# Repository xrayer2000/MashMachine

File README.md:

# MashMachine

An automated homebrewing system developed around a modified Vevor mash tun, an ESP32-based controller and custom temperature regulation.

## Introduction

This project has been a great journey for me to learn even more about the subjects covered in the MPSYS (Systems, Control and Mechatronics) programme at Chalmers University of Technology.

I have specifically applied knowledge from two courses:

- **SSY230 – System Identification**
- **SSY285 – Design of Linear Control Systems**

The mash tun has served as a physical test platform for applying system identification and control theory to a real-world thermal system.

## Mash Tun Construction

The starting point for this project was a relatively basic mash tun from Vevor, which only supported simple heating through its original controller.

I decided to modify the vessel and develop a custom control system to improve temperature regulation and automate the brewing process.

The mechanical work involved modifying the stainless-steel vessel, welding components, installing the necessary hardware and constructing an insulated enclosure.

### Fabrication

The following photographs document parts of the fabrication process, including the initial measurements, stainless-steel vessel and welding.

### Welding and Assembly

### Finished Mash Tun

The finished vessel has an insulated exterior to reduce heat losses and improve thermal efficiency.

### Construction Videos

#### Welding

https://github.com/user-attachments/assets/f25a4e15-6e44-4505-bbf4-2bfe34d7de5a

https://github.com/user-attachments/assets/1c13a10b-537a-4cbe-8e05-aff711293a5b

## System Implementation

The original controller was removed and replaced with a custom-built ESP32-based control system.

Several hardware modifications were made:

- A circulation system was added using a pump.
- Piping was installed to allow continuous wort circulation.
- The original control electronics were replaced with an ESP32-based system.

The circulation system improves temperature uniformity and makes the system more suitable for model-based control.

The original system exhibited temperature overshoot of around 2°C. With the new controller, temperature regulation is significantly improved, with essentially no observable overshoot under normal operating conditions.

Additional functionality includes:

- Hop timers
- Mash programs
- Automated process control
- Home Assistant integration

## System Identification

In the System Identification course, I used the mash tun to collect both estimation and validation data.

Using the System Identification Toolbox in MATLAB, I derived state-space models for three different operating points:

- 50°C
- 65°C
- 70°C

### Estimation Data

### Validation Data

### ARMAX Model

All system matrices were computed in MATLAB and then implemented directly on the ESP32. The computational work was therefore performed offline rather than on the microcontroller.

## Control System Design

Once the state-space models had been obtained, I used the concepts from Design of Linear Control Systems to design controllers based on the identified models.

I initially implemented a state-feedback LQR controller and later extended it to an LQG controller by adding a Kalman filter for state estimation.

LQG requires an explicit state-space representation of the system dynamics. Unlike conventional PID control, which operates on the control error, LQG uses a model to estimate internal system states and calculate the control input.

However, the LQG controller turned out to be somewhat excessive for this application, since the system exhibits slow and stable thermal dynamics. A well-tuned PID controller would likely have been sufficient.

## Measurement System

The system initially used an NTC thermistor. This approach was eventually abandoned due to calibration difficulties and unreliable measurements.

### NTC Thermistor

The NTC sensor is strongly nonlinear and requires reliable calibration points consisting of temperature and resistance.

In practice, this introduced several problems:

- Calibration was sensitive to measurement noise.
- Small resistance errors could result in significant temperature errors.
- Obtaining consistent and accurate reference temperatures was difficult.

These issues resulted in deviations between measured and actual temperatures.

### PT100

The NTC was replaced with a PT100 resistance temperature detector (RTD).

The main reasons were:

- More linear temperature-resistance characteristics.
- More straightforward calibration.
- Stable and predictable measurements.

This change significantly improved the quality of the temperature measurements, which is particularly important for system identification and state estimation.

## Home Assistant Integration

The system is integrated with Home Assistant for monitoring and interaction.

A local Linux machine acts as a small server, running Home Assistant in a Docker container. The same setup also runs supporting services such as InfluxDB and Grafana.

Communication between the ESP32 and Home Assistant is handled using MQTT.

This setup enables:

- Real-time monitoring of temperature, control signals and system states.
- Logging data to InfluxDB for further analysis.
- Visualization of system behaviour in Grafana.
- Remote interaction through the Home Assistant interface.

The integration is useful not only for convenience, but also for collecting experimental data and observing controller performance over time.

## System Characteristics

The mash tun exhibits slow dynamics and significant thermal inertia.

Measurements are also affected by noise, making aggressive control unsuitable.

As a result, stability and consistent temperature regulation are more important than fast response.

## Challenges and Lessons Learned

The main difficulty in this project was not the controller design itself.

The most challenging aspects were:

- Obtaining reliable measurement data.
- Constructing a model that accurately represents the real system.
- Handling non-ideal behaviour in a physical system.
- Integrating mechanical, electrical and software components.

The project has provided an opportunity to apply theoretical concepts from system identification and control engineering to a practical application.

## Results

- Modified and insulated stainless-steel mash tun.
- Custom ESP32-based control system.
- Experimental system identification at multiple operating temperatures.
- State-space models derived using MATLAB.
- Implemented LQR and LQG controllers.
- Improved temperature measurement using a PT100.
- Significantly improved temperature regulation.
- Home Assistant, MQTT, InfluxDB and Grafana integration.

## Acknowledgements

A special thanks to my dad for giving me the opportunity to carry out the welding work at his workplace, **MTA Sahlgrenska**. His help made the fabrication of the stainless-steel mash tun possible, and I really appreciate his support throughout the project.

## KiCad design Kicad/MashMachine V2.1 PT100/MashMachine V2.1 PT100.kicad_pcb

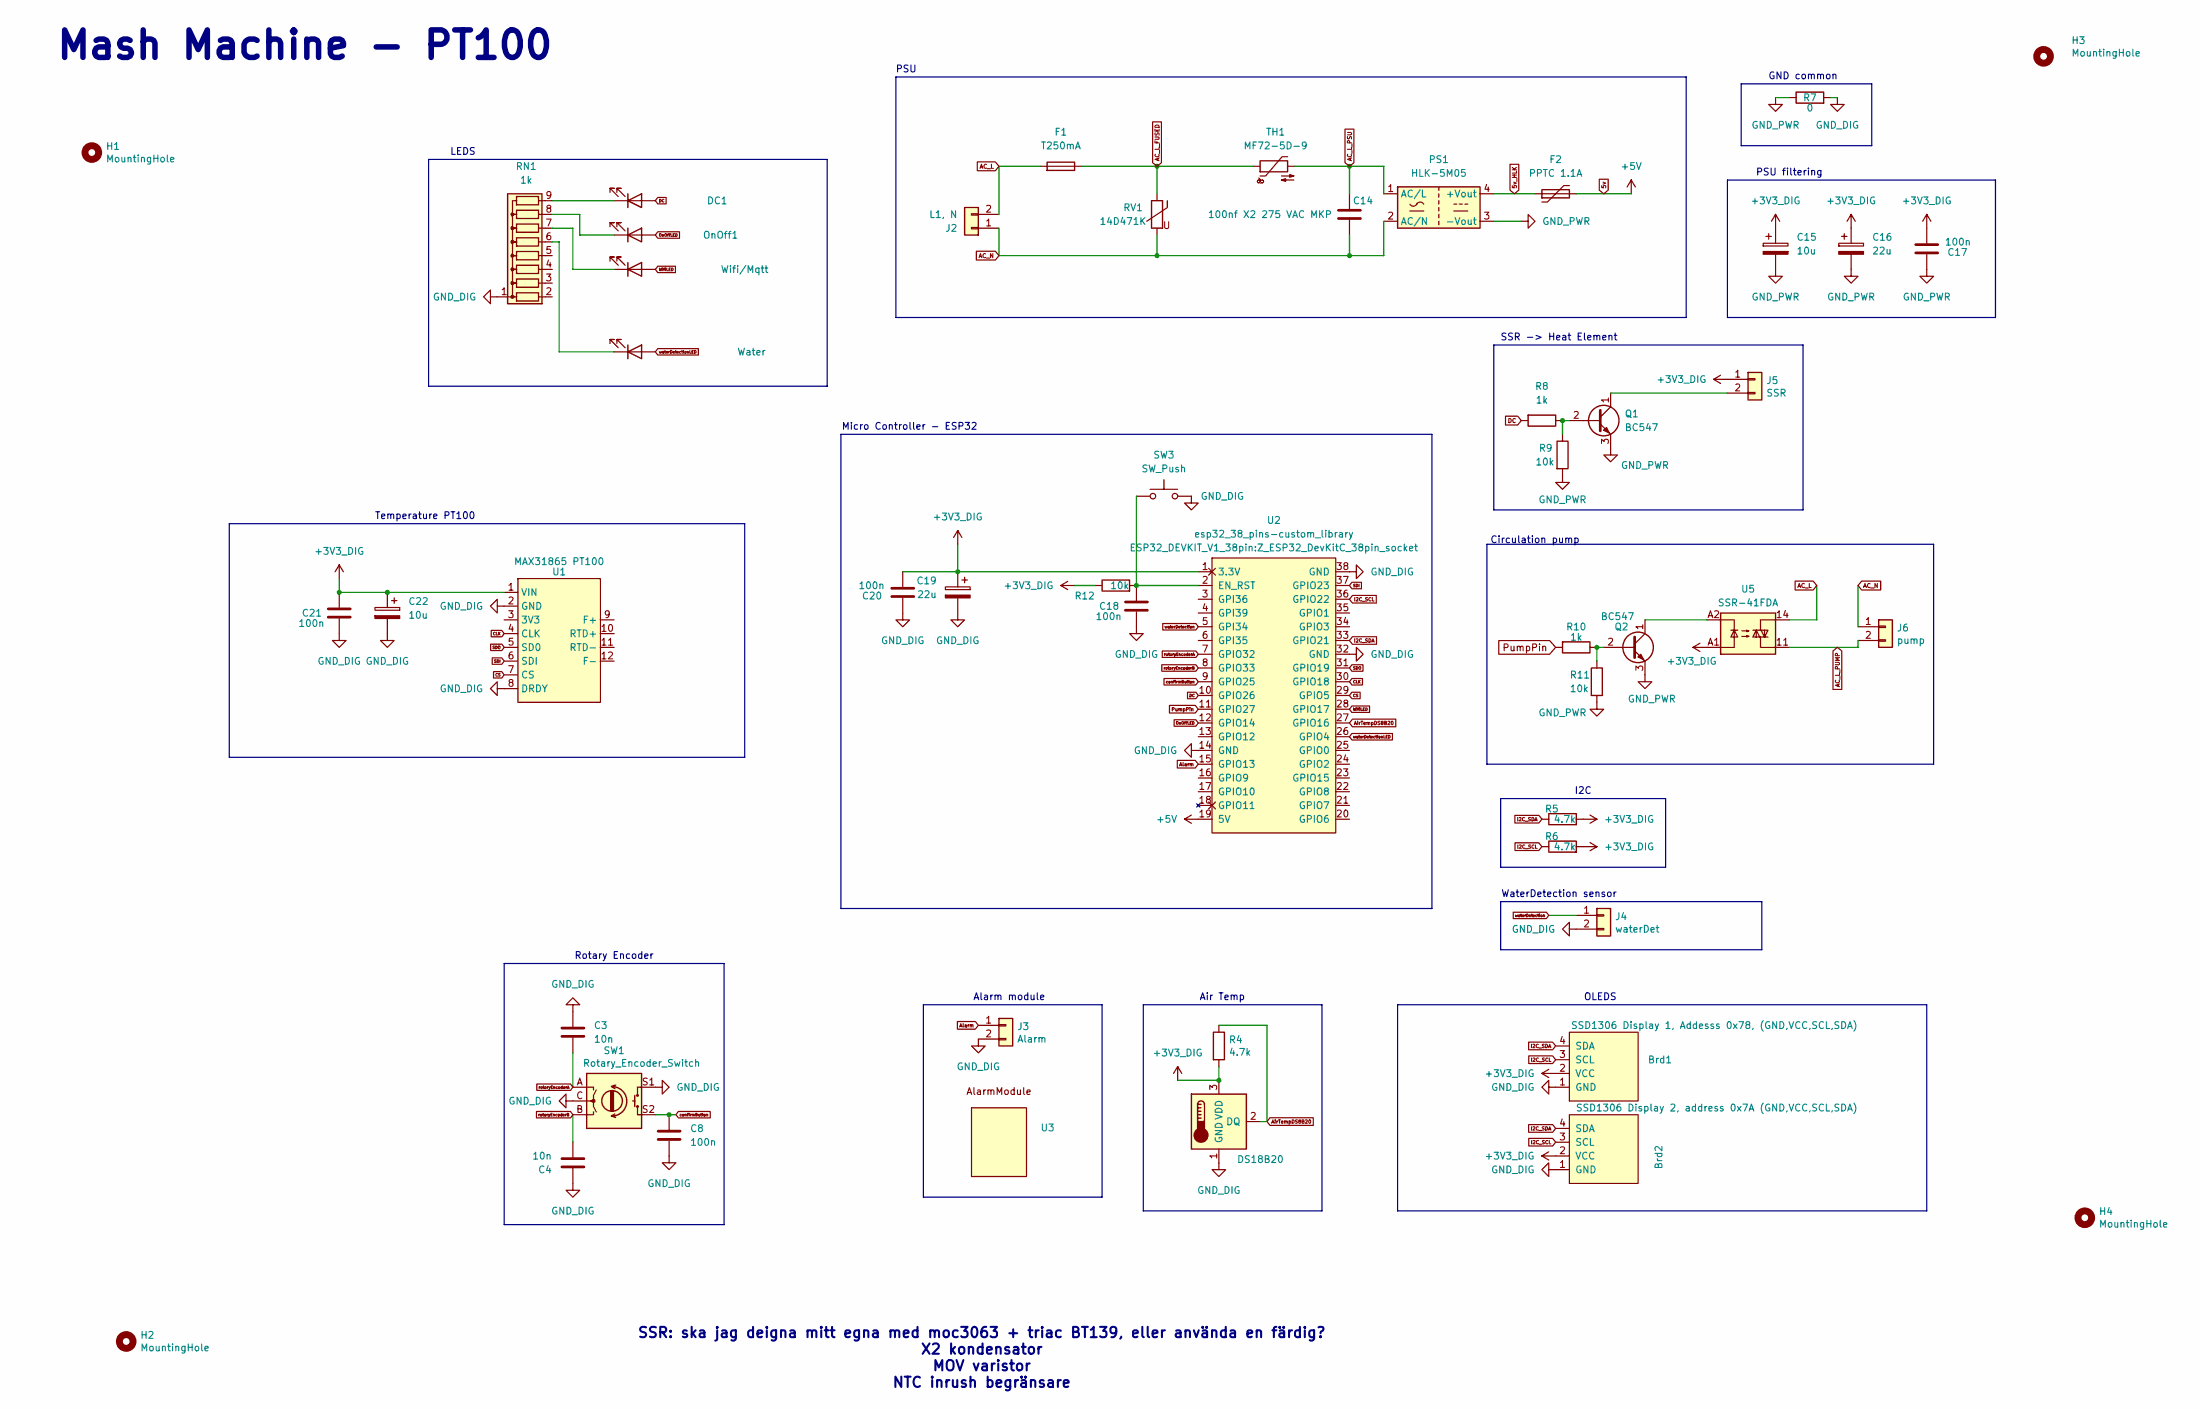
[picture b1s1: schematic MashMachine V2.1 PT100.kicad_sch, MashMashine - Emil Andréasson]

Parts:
Air_temp1: DS18B20; TO-92L_Inline
Brd1: SSD1306 Display 1, Addesss 0x78, (GND,VCC,SCL,SDA); ssd1306_1.3''
Brd2: SSD1306 Display 2, address 0x7A (GND,VCC,SCL,SDA); ssd1306_1.3''
C3, C4: 10n; C_Disc_D3.0mm_W1.6mm_P2.50mm
C8, C17, C18, C20, C21: 100n; C_Disc_D3.0mm_W1.6mm_P2.50mm
C14: 100nf X2 275 VAC MKP; C_Rect_L16.5mm_W6.0mm_P15.00mm_MKT
C15, C22: 10u; CP_Radial_D4.0mm_P2.00mm
C16, C19: 22u; CP_Radial_D4.0mm_P2.00mm
DC1: DC; LED_D3.0mm
F1: T250mA; Fuseholder5x20_horiz_SemiClosed_Casing10x25mm
F2: PPTC 1.1A; Fuse_BelFuse_0ZRE0016FF_L9.9mm_W3.8mm
H1, H2, H3, H4: MountingHole; MountingHole_3.2mm_M3_DIN965_Pad
J2: L1, N; TerminalBlock_RND_205-00287_1x02_P5.08mm_Horizontal
J3: Alarm; JST_XH_B2B-XH-A_1x02_P2.50mm_Vertical
J4: waterDet; JST_XH_B2B-XH-A_1x02_P2.50mm_Vertical
J5: SSR; JST_XH_B2B-XH-A_1x02_P2.50mm_Vertical
J6: pump; TerminalBlock_RND_205-00287_1x02_P5.08mm_Horizontal
LED1: Wifi/Mqtt; LED_D3.0mm
LED3: Water; LED_D3.0mm
OnOff1: On; LED_D3.0mm
PS1: HLK-5M05; Converter_ACDC_Hi-Link_HLK-5Mxx
Q1, Q2: BC547; TO-92_Inline
R4, R5, R6: 4.7k; R_Axial_DIN0204_L3.6mm_D1.6mm_P2.54mm_Vertical
R7: 0; R_Axial_DIN0204_L3.6mm_D1.6mm_P1.90mm_Vertical
R8, R10: 1k; R_Axial_DIN0204_L3.6mm_D1.6mm_P2.54mm_Vertical
R9, R11: 10k; R_Axial_DIN0204_L3.6mm_D1.6mm_P2.54mm_Vertical
R12: 10k; R_Axial_DIN0207_L6.3mm_D2.5mm_P7.62mm_Horizontal
RN1: 1k; R_Array_SIP9
RV1: 14D471K; RV_Disc_D15.5mm_W4.5mm_P7.5mm
SW1: Rotary_Encoder_Switch; RotaryEncoder_Alps_EC11E-Switch_Vertical_H20mm
SW3: SW_Push; SW_PUSH_6mm
TH1: MF72-5D-9; RV_Disc_D9mm_W5.2mm_P5mm
U1: MAX31865 PT100; PinSocket_1x08_P2.54mm_Vertical
U2: esp32_38_pins-custom_library; Z_ESP32_DevKitC_38pin_socket
U3: AlarmModule
U5: SSR-41FDA; Finder_34.81

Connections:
5v: F2.2, U2.19 (5V)
5v_HLK: F2.1, PS1.4 (+Vout)
+3V3_DIG: Air_temp1.3 (VDD), Brd1.2 (VCC), Brd2.2 (VCC), C15.1, C16.1, C17.2, C19.1, C20.2, C21.2, C22.1, J5.1, R4.2, R5.2, R6.2, R12.1, U1.1 (VIN), U2.1 (3.3V), U5.A1
AC_L: F1.2, J2.2, U5.14
AC_L_FUSED: F1.1, RV1.1, TH1.1
AC_L_PSU: C14.1, PS1.1 (AC/L), TH1.2
AC_L_PUMP: J6.2, U5.11
AC_N: C14.2, J2.1, J6.1, PS1.2 (AC/N), RV1.2
AirTempDS8B20: Air_temp1.2 (DQ), R4.1, U2.27 (GPIO16)
Alarm: J3.1, U2.15 (GPIO13)
CLK: U1.4 (CLK), U2.30 (GPIO18)
CS: U1.7 (CS), U2.29 (GPIO5)
DC: DC1.2 (A), R8.2, U2.10 (GPIO26)
GND_DIG: Air_temp1.1 (GND), Brd1.1 (GND), Brd2.1 (GND), C3.2, C4.2, C8.2, C18.1, C19.2, C20.1, C21.1, C22.2, J3.2, J4.2, R7.2, RN1.1 (common), SW1.C, SW1.S1, SW3.2, U1.2 (GND), U1.8 (DRDY), U2.14 (GND), U2.32 (GND), U2.38 (GND)
GND_PWR: C15.2, C16.2, C17.1, PS1.3 (-Vout), Q1.3 (E), Q2.3 (E), R7.1, R9.2, R11.2
I2C_SCL: Brd1.3 (SCL), Brd2.3 (SCL), R6.1, U2.36 (GPIO22)
I2C_SDA: Brd1.4 (SDA), Brd2.4 (SDA), R5.1, U2.33 (GPIO21)
unnamed: DC1.1 (K), RN1.9 (R8)
unnamed: J5.2, Q1.1 (C)
unnamed: LED1.1 (K), RN1.7 (R6)
unnamed: LED3.1 (K), RN1.6 (R5)
unnamed: OnOff1.1 (K), RN1.8 (R7)
unnamed: Q1.2 (B), R8.1, R9.1
unnamed: Q2.2 (B), R10.1, R11.1
unnamed: Q2.1 (C), U5.A2
unnamed: C18.2, R12.2, SW3.1, U2.2 (EN_RST)
OnOffLED: OnOff1.2 (A), U2.12 (GPIO14)
PumpPin: R10.2, U2.11 (GPIO27)
SDI: U1.6 (SDI), U2.37 (GPIO23)
SDO: U1.5 (SD0), U2.31 (GPIO19)
WifiLED: LED1.2 (A), U2.28 (GPIO17)
confirmButton: C8.1, SW1.S2, U2.9 (GPIO25)
rotoryEncoderA: C3.1, SW1.A, U2.7 (GPIO32)
rotoryEncoderB: C4.1, SW1.B, U2.8 (GPIO33)
waterDetection: J4.1, U2.5 (GPI34)
waterDetectionLED: LED3.2 (A), U2.26 (GPIO4)

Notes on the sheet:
LEDS
GND common
Rotary Encoder
OLEDS
Micro Controller - ESP32
Circulation pump
SSR -> Heat Element
Alarm module
Air Temp
Mash Machine - PT100
PSU filtering
SSR: ska jag deigna mitt egna med moc3063 + triac BT139, eller använda en färdig? X2 kondensator MOV varistor NTC inrush begränsare
PSU
WaterDetection sensor
I2C
Temperature PT100

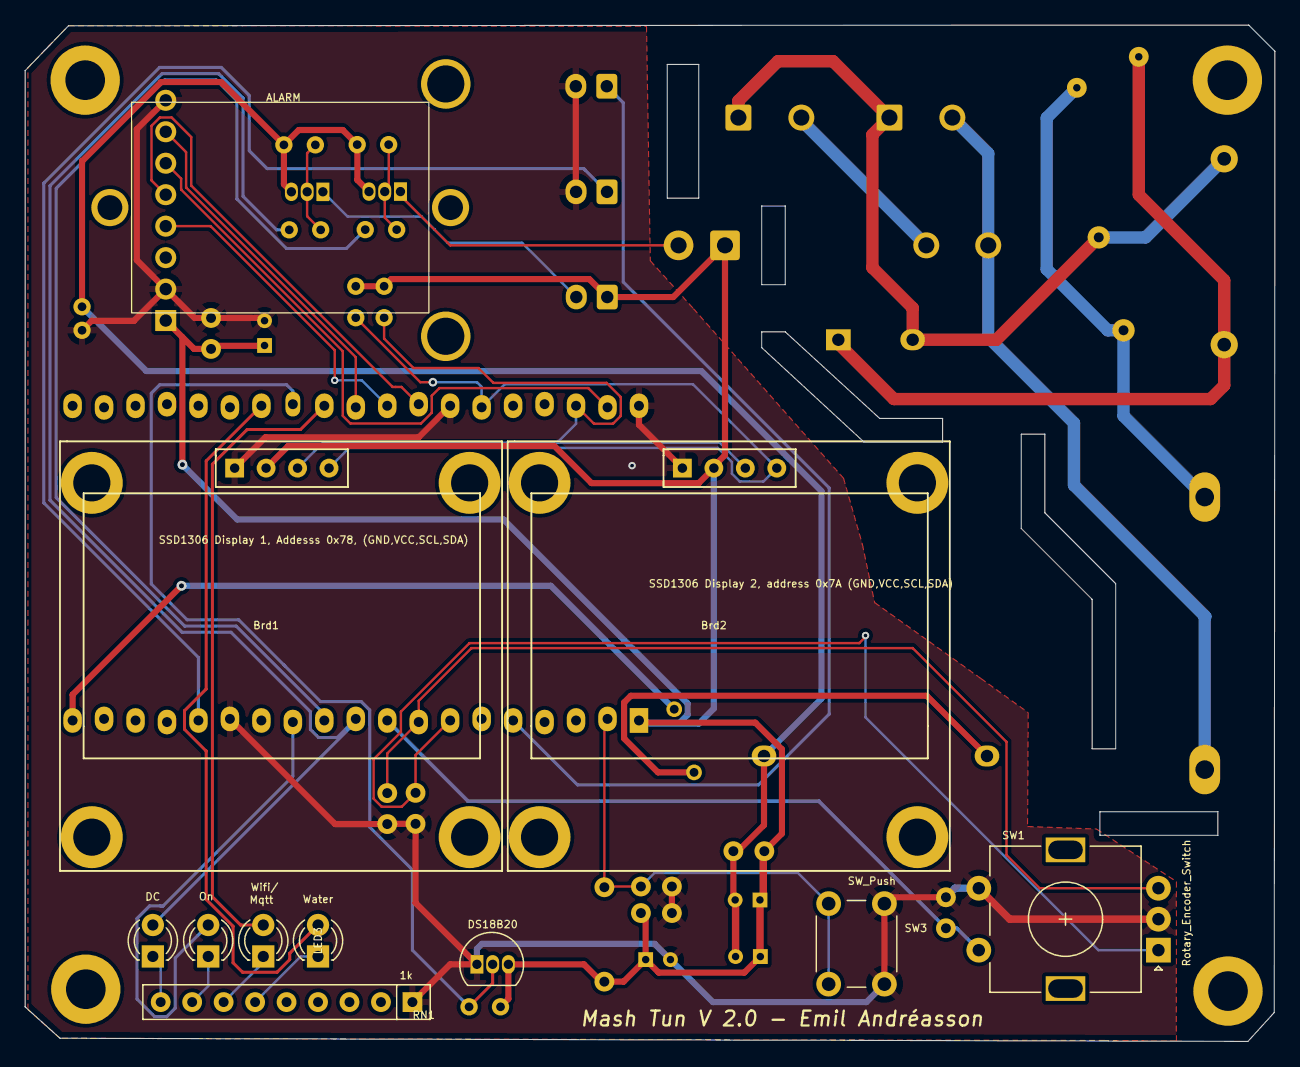
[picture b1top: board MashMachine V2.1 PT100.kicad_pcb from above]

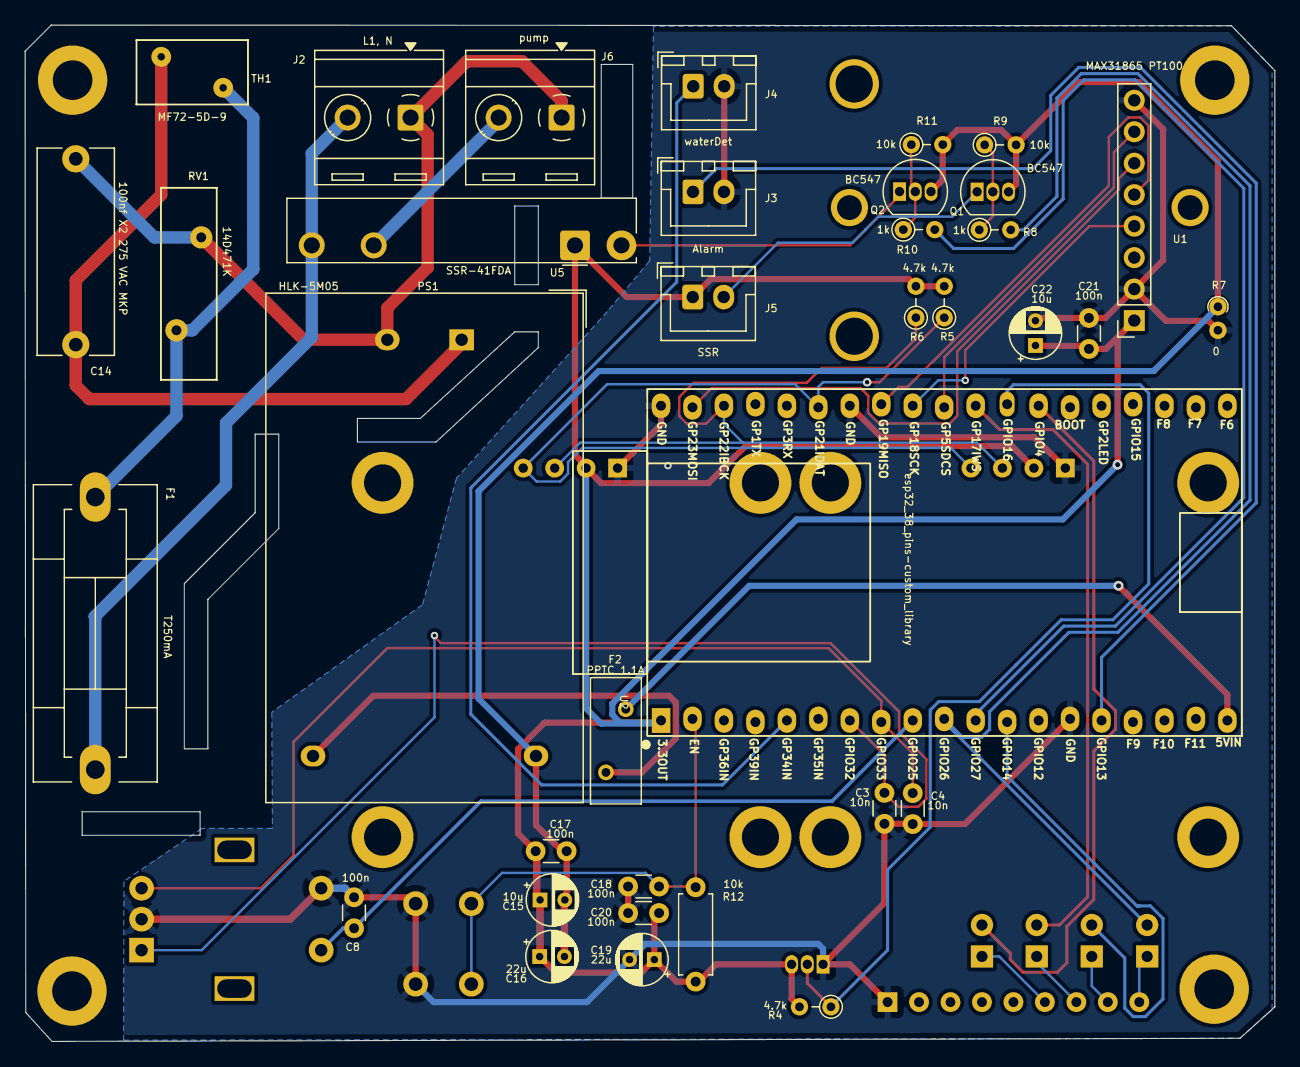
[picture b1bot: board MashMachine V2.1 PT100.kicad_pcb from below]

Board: 2 copper layers, 100.9 x 82.0 mm, 51 parts (36 on the bottom side), 36 nets.

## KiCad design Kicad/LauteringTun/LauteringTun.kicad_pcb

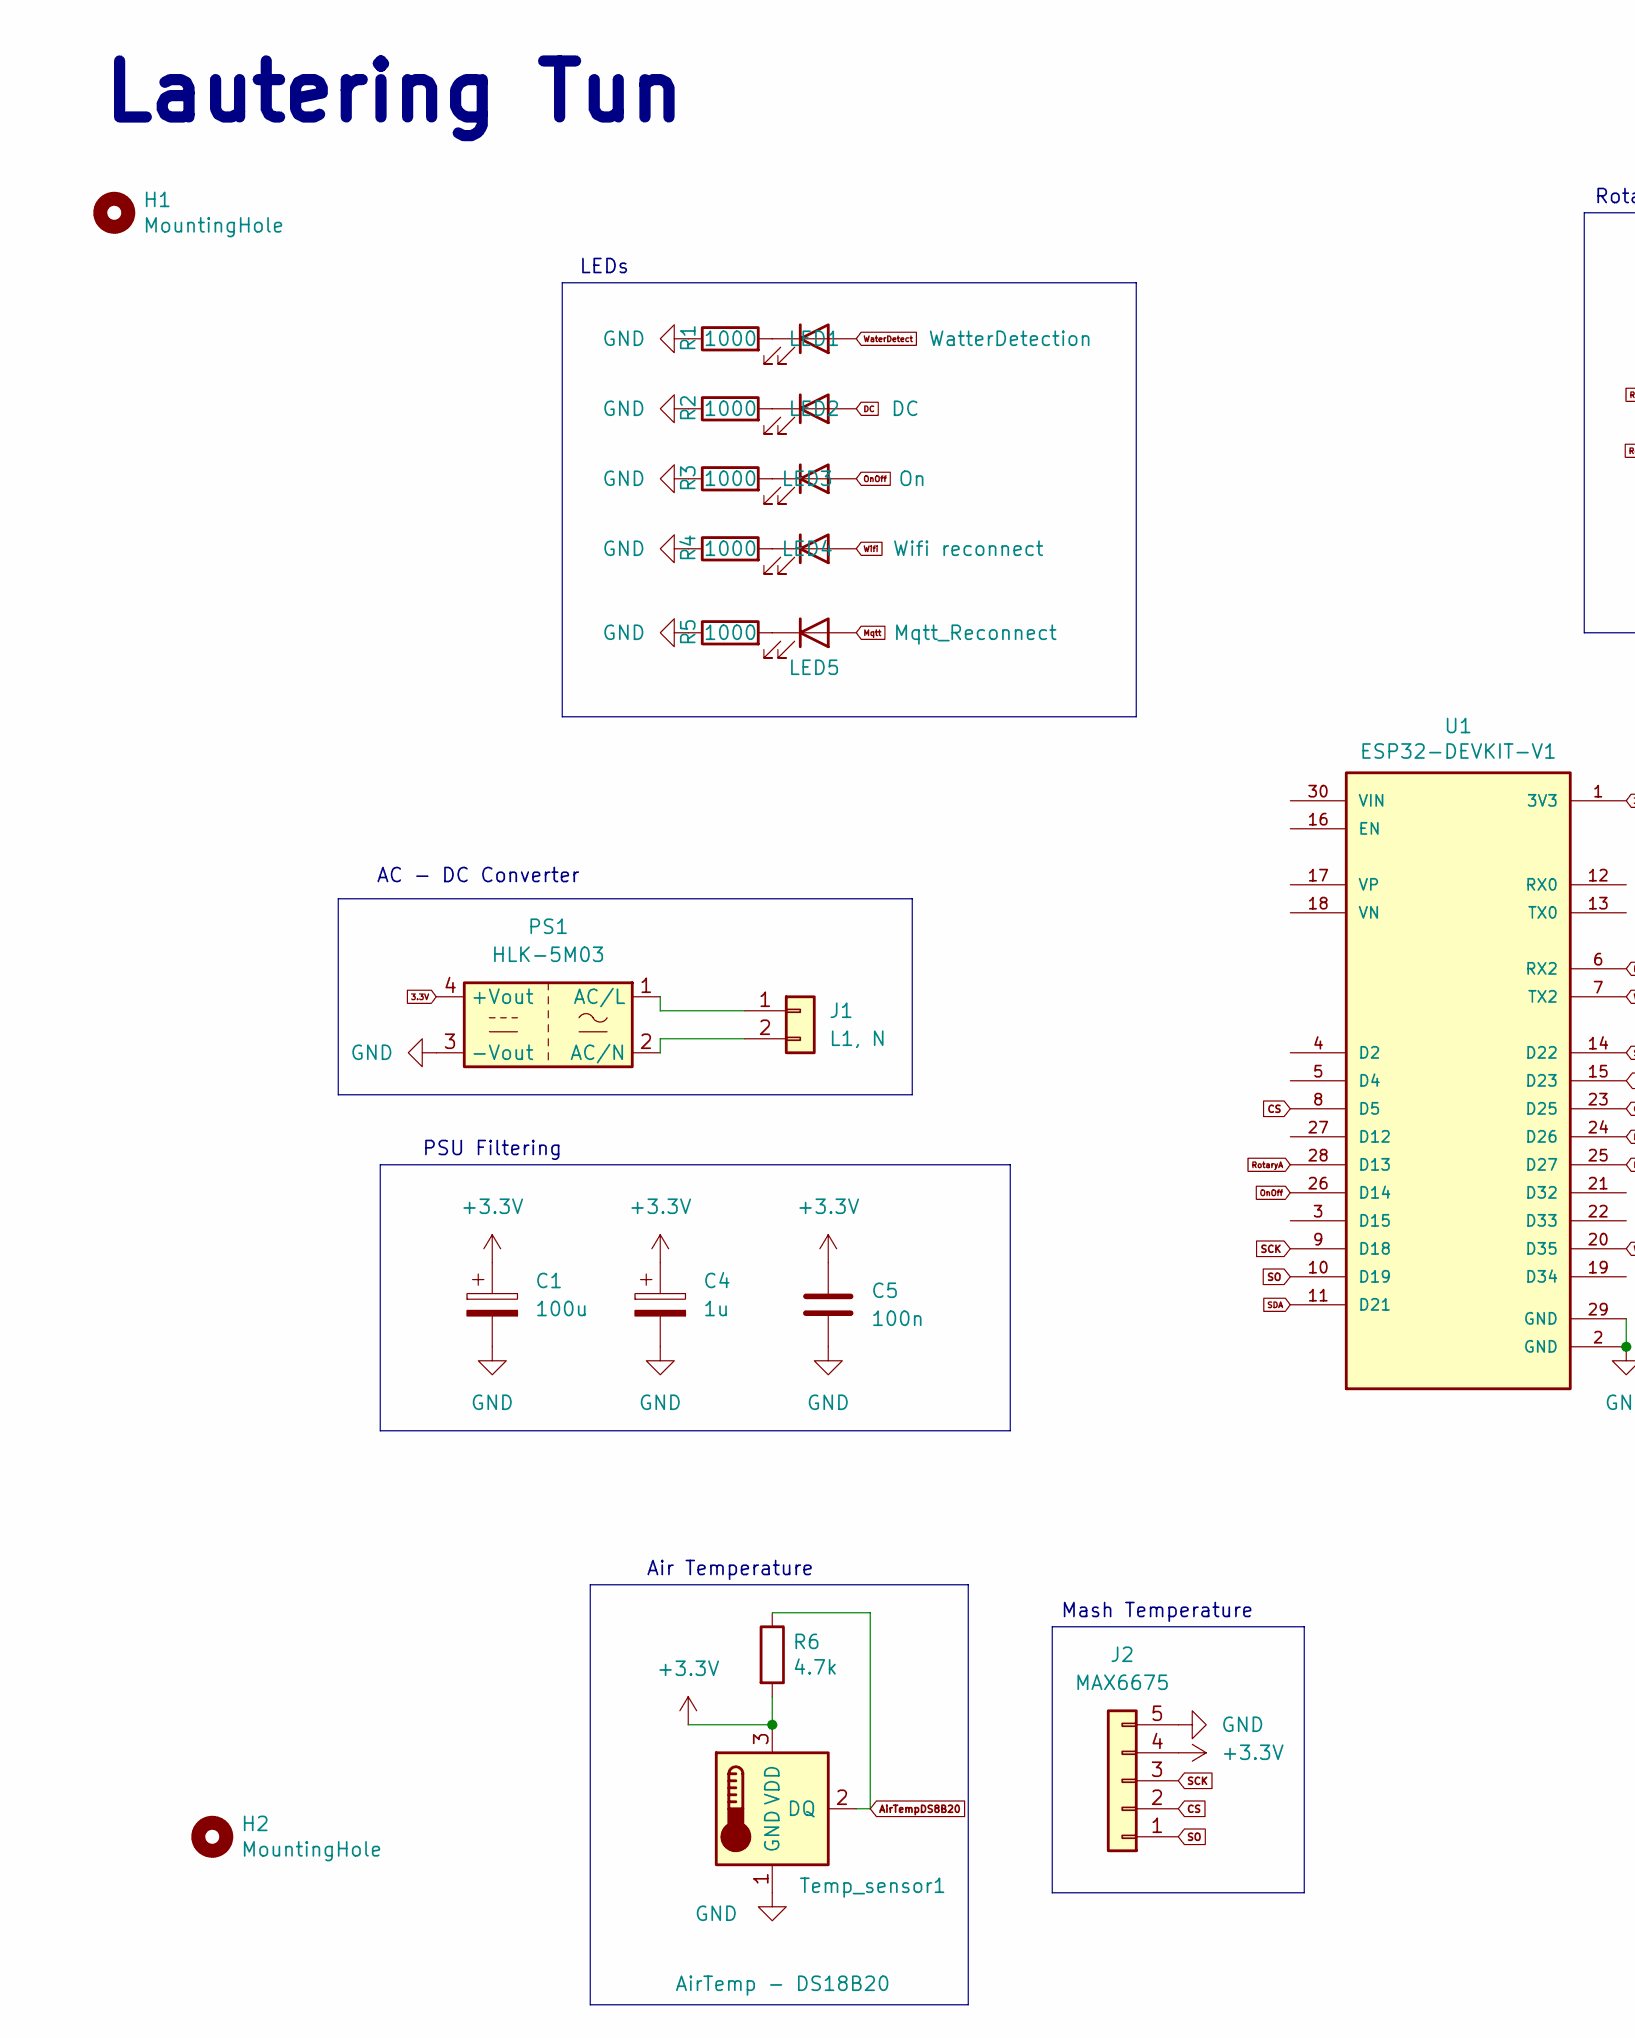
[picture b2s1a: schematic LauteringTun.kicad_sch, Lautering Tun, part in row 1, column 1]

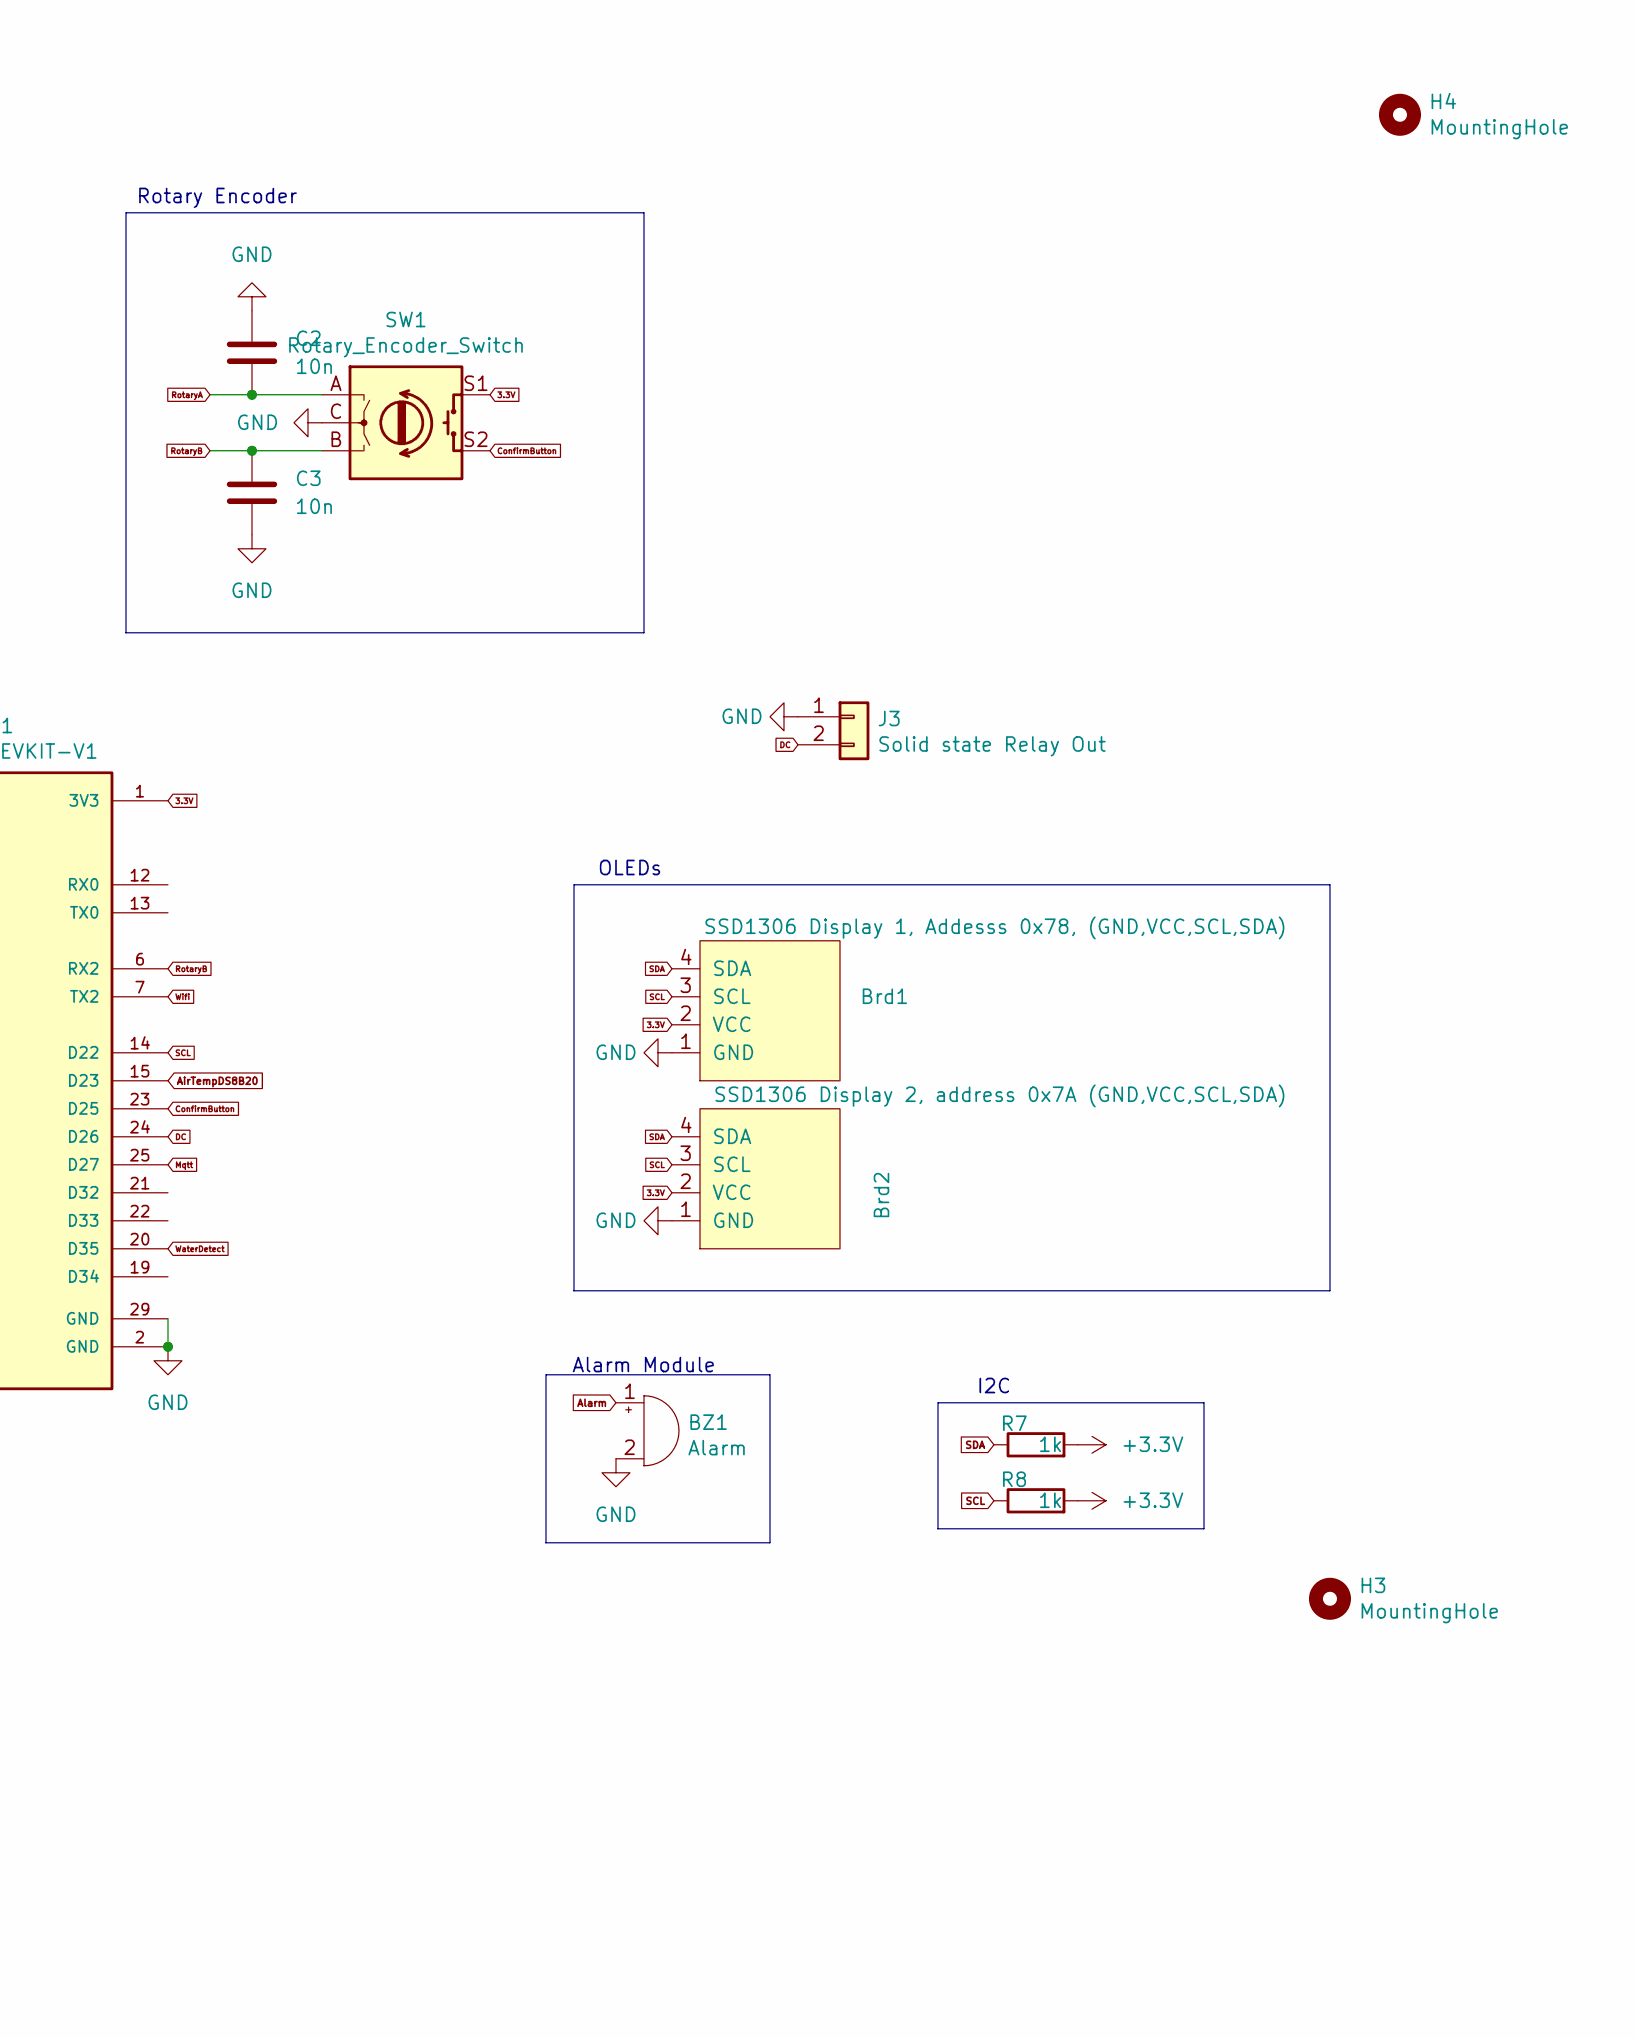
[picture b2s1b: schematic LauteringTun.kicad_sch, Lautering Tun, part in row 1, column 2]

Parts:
BZ1: Alarm; Buzzer_12x9.5RM7.6
Brd1: SSD1306 Display 1, Addesss 0x78, (GND,VCC,SCL,SDA); ssd1306_1.3''
Brd2: SSD1306 Display 2, address 0x7A (GND,VCC,SCL,SDA); ssd1306_1.3''
C1: 100u; CP_Radial_D4.0mm_P2.00mm
C2, C3: 10n; C_Disc_D3.0mm_W1.6mm_P2.50mm
C4: 1u; CP_Radial_D4.0mm_P2.00mm
C5: 100n; C_Disc_D3.0mm_W1.6mm_P2.50mm
H1, H2, H3, H4: MountingHole; MountingHole_3.2mm_M3_DIN965_Pad
J1: L1, N; TerminalBlock_Phoenix_MKDS-1,5-2_1x02_P5.00mm_Horizontal
J2: MAX6675
J3: Solid state Relay Out; JST_XH_B2B-XH-A_1x02_P2.50mm_Vertical
LED1: WatterDetection; LED_D3.0mm
LED2: DC; LED_D3.0mm
LED3: On; LED_D3.0mm
LED4: Wifi reconnect; LED_D3.0mm
LED5: Mqtt_Reconnect; LED_D3.0mm
PS1: HLK-5M03; Converter_ACDC_Hi-Link_HLK-5Mxx
R1, R2, R3, R4, R5: 1000; R_Axial_DIN0207_L6.3mm_D2.5mm_P7.62mm_Horizontal
R6: 4.7k; R_Axial_DIN0207_L6.3mm_D2.5mm_P10.16mm_Horizontal
R7, R8: 1k; R_Axial_DIN0207_L6.3mm_D2.5mm_P7.62mm_Horizontal
SW1: Rotary_Encoder_Switch; RotaryEncoder_Alps_EC11E-Switch_Vertical_H20mm
Temp_sensor1: AirTemp - DS18B20; TO-92L_Inline
U1: ESP32-DEVKIT-V1; ESP32_DEVKIT_V1; PARTREV N/A

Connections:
3.3V: Brd1.2 (VCC), Brd2.2 (VCC), PS1.4 (+Vout), SW1.S1, U1.1 (3V3)
+3.3V: C1.1, C4.1, C5.2, J2.4, R6.2, R7.2, R8.2, Temp_sensor1.3 (VDD)
AirTempDS8B20: R6.1, Temp_sensor1.2 (DQ), U1.15 (D23)
Alarm: BZ1.1 (-)
CS: J2.2, U1.8 (D5)
ConfirmButton: SW1.S2, U1.23 (D25)
DC: J3.2, LED2.2 (A), U1.24 (D26)
GND: BZ1.2 (+), Brd1.1 (GND), Brd2.1 (GND), C1.2, C2.2, C3.1, C4.2, C5.1, J2.5, J3.1, PS1.3 (-Vout), R1.1, R2.1, R3.1, R4.1, R5.1, SW1.C, Temp_sensor1.1 (GND), U1.2 (GND), U1.29 (GND)
Mqtt: LED5.2 (A), U1.25 (D27)
unnamed: J1.1, PS1.1 (AC/L)
unnamed: J1.2, PS1.2 (AC/N)
unnamed: LED1.1 (K), R1.2
unnamed: LED2.1 (K), R2.2
unnamed: LED3.1 (K), R3.2
unnamed: LED4.1 (K), R4.2
unnamed: LED5.1 (K), R5.2
OnOff: LED3.2 (A), U1.26 (D14)
RotaryA: C2.1, SW1.A, U1.28 (D13)
RotaryB: C3.2, SW1.B, U1.6 (RX2)
SCK: J2.3, U1.9 (D18)
SCL: Brd1.3 (SCL), Brd2.3 (SCL), R8.1, U1.14 (D22)
SDA: Brd1.4 (SDA), Brd2.4 (SDA), R7.1, U1.11 (D21)
SO: J2.1, U1.10 (D19)
WaterDetect: LED1.2 (A), U1.20 (D35)
Wifi: LED4.2 (A), U1.7 (TX2)

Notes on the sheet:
I2C
Alarm Module
AC - DC Converter
Air Temperature
Lautering Tun
OLEDs
Mash Temperature
LEDs
PSU Filtering
Rotary Encoder

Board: 2 copper layers, 32 parts (2 on the bottom side), 24 nets, no tracks yet.
